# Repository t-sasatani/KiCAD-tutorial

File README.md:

# KiCad tutorial

## Content (what we will make)
- Make a simple wireless power receiver circuit that lights up an LED light bulb.
- (I might add some other circuit examples by the workshop.)

## What you will learn
- The minimum workflow for using KiCad
- How to place orders to PCB manufactures
- Some elementary tips for prototyping circuits
- Final design files ([schematic](/KiCad/export/sch.pdf), [board](/KiCad/export/brd.pdf))

## What you won't learn
- Circuit design (parts selection, patterning, etc.)

# To do before workshop

## Download KiCad
- [KiCAD](https://www.kicad.org/): I'm using version 8.0.2.

## Watch short tutorial video (optional)
About 13 min

# Hands-on workshop

## Typical workflow
DRC: Design rule check
```mermaid
flowchart TD
    B[Import/create parts] --> C[Make schematic]
    C --> B
    C --> G[Define DRC]
    G --> D[Pattern board]
    D --> C
    D --> E{DRC}
    E --> |NG| D
    E --> |OK| F{Fab review}
    F --> |NG| D
    F --> |OK| H[Order]
```

## Sketch circuit
- Roughly determine the core components you will use
    - Be careful of the availability of parts, etc
- For my case, I hand write a sketch
- We'll skip this in this tutorial

## Import/create parts
- We will use components pre-loaded in KiCad, so we'll skip this part
- If you want to make parts, watch the following video.
    - TBD

## Make schematic
### Place the components
[Schematic PDF](/KiCad/export/sch.pdf)

- **LDO: Voltage regulator (U1)**
    - Symbol: NCP1117-ADJ_SOT223
    - Footprint: Package_TO_SOT_SMD:SOT-223-3_TabPin2
    - [Digikey](https://www.digikey.jp/product-detail/ja/on-semiconductor/NCP1117STAT3G/NCP1117STAT3GOSCT-ND/1967218)

- **Ground: GND**
    - Symbol: GND

- **Tantalum Capacitors (C1, C2)**
    - Symbol: C_Polarized
    - Footprint: Capacitor_Tantalum_SMD:CP_EIA-3216-10_Kemet-I_Pad1.58x1.35mm_HandSolder
        - C1 = 10 uF, 25V, tant
        - C2 = 10 uF, 10V, tant
    - [Digikey-1](https://www.digikey.jp/ja/products/detail/kemet/T491A106M020AT/1739472)
    - [Digikey-2](https://www.digikey.jp/ja/products/detail/kemet/T491A106K010AT/818545)

- **Feedback resistor (R1, R2)**
    - Symbol: R
    - Footprint: Resistor_SMD:R_0603_1608Metric_Pad0.98x0.95mm_HandSolder
    - **Quiz: tune the output voltage to 9V, looking at the [LDO datasheet](https://www.onsemi.com/pdf/datasheet/ncp1117-d.pdf)**
        - R1 = ?
        - R2 = ?

- **Diode (D1, D2, D3, D4)**
    - Symbol: PMEG6010CEH
    - Footprint: Diode_SMD:D_SOD-123F
    - [Digikey](https://www.digikey.jp/product-detail/ja/nexperia-usa-inc/PMEG6010CEH-115/1727-3848-1-ND/1589917)

- **SMA connector (J1)**
    - Symbol: Conn_Coaxial
    - Footprint: Connector_Coaxial:SMA_Amphenol_901-143_Horizontal
    - [Digikey](https://www.digikey.jp/products/ja?keywords=60311002114501)

- **Ceramic capacitors: (C3, C4, C5, C6)**
    - Symbol: C
    - Footprint: Capacitor_SMD:C_0603_1608Metric_Pad1.08x0.95mm_HandSolder
    - Values
        - C3 = 1000 pF
        - C4 = 0.1 uF
        - C5 = DNP
        - C6 = 0.1 uF

- **Test point: (TP1-TP8)**
    - Symbol: TestPoint
    - Footprint: TestPoint:TestPoint_Keystone_5000-5004_Miniature
    - Vout is also this pin.

- **Mounting hole (H1-H4)**
    - Symbol: MountingHole
    - MountingHole:MountingHole_3.2mm_M3

### Tips
- Name the wires
    - This makes complex designs easier, so lets make it your habit.

## Pattern board

### Constraints
Below are just examples. You'll need to check factory design rules (for PCBWay, you can check the [PCB Instant Quote](https://www.pcbway.com/orderonline.aspx) page).
- PCBWay: https://www.pcbway.com/capabilities.html

### Board layout
[Board layout PDF](/KiCad/export/brd.pdf)

### Check in 3-D CAD
- Look for mechanical intersections, etc.

## Send to fab
- [PCBWay](https://www.pcbway.com/) and [Login information](https://sites.google.com/a/akg.t.u-tokyo.ac.jp/wiki) of lab account
- Use [PCBWay plug-in for KiCad](https://github.com/pcbway/PCBWay-Plug-in-for-Kicad)
- Try out gerber viewer (beta)
    - https://www.pcbway.com/project/OnlineGerberViewer.html

# Misc

## Links
- https://componentsearchengine.com/

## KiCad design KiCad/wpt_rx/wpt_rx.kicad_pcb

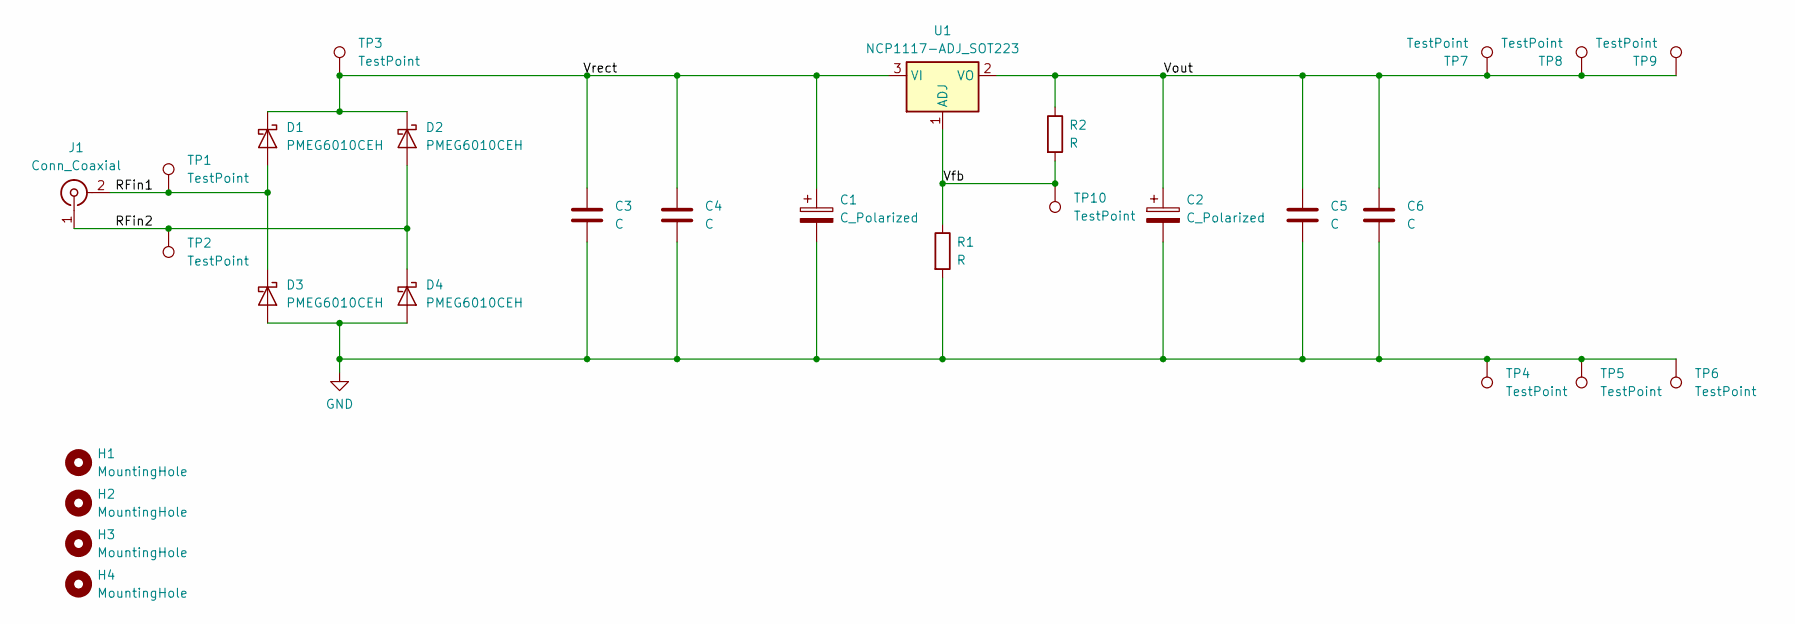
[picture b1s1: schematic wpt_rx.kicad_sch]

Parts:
C1, C2: C_Polarized; CP_EIA-3216-10_Kemet-I_Pad1.58x1.35mm_HandSolder
C3, C4, C5, C6: C; C_0603_1608Metric_Pad1.08x0.95mm_HandSolder
D1, D2, D3, D4: PMEG6010CEH; D_SOD-123F
H1, H2, H3, H4: MountingHole; MountingHole_3.2mm_M3
J1: Conn_Coaxial; SMA_Amphenol_901-143_Horizontal
R1, R2: R; R_0603_1608Metric_Pad0.98x0.95mm_HandSolder
TP1, TP2, TP3, TP4, TP5, TP6, TP7, TP8, TP9, TP10: TestPoint; TestPoint_Keystone_5000-5004_Miniature
U1: NCP1117-ADJ_SOT223; SOT-223-3_TabPin2

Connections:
/RFin1: D1.2 (A), D3.1 (K), J1.2 (Ext), TP1.1
/RFin2: D2.2 (A), D4.1 (K), J1.1 (In), TP2.1
/Vfb: R1.1, R2.2, TP10.1, U1.1 (ADJ)
/Vout: C2.1, C5.1, C6.1, R2.1, TP7.1, TP8.1, TP9.1, U1.2 (VO)
/Vrect: C1.1, C3.1, C4.1, D1.1 (K), D2.1 (K), TP3.1, U1.3 (VI)
GND: C1.2, C2.2, C3.2, C4.2, C5.2, C6.2, D3.2 (A), D4.2 (A), R1.2, TP4.1, TP5.1, TP6.1

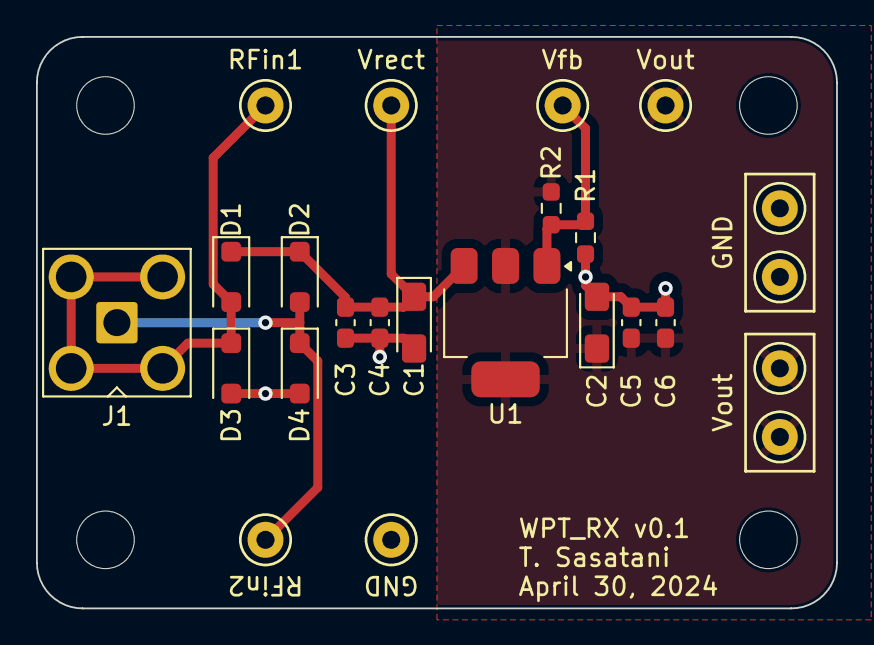
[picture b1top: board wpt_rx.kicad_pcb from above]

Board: 2 copper layers, 44.4 x 31.8 mm, 28 parts (0 on the bottom side), 6 nets.

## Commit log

2024-04-30 Put together a simple tutorial
2024-04-30 add gitignore
2024-04-30 add file exports
2024-04-30 Create LICENSE
2024-04-30 Update LICENSE
2024-04-30 add reference video
2024-04-30 minor changes
2024-04-30 minor updates
2024-05-01 bump kicad version to 8.0.2, etc.
2024-05-01 add sch/brd pdf
